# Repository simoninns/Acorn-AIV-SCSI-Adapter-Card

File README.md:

# Acorn-AIV-SCSI-Adapter-Card
A reproduction of the original Acorn AIV SCSI Adapter Card in KiCAD (as used in the BBC Domesday System)

For more information please see the [project wiki pages](https://github.com/simoninns/Acorn-AIV-SCSI-Adapter-Card/wiki)

## Synopsis

This card is designed as a drop-in replacement for the original Acorn card in the BBC Master Microcomputer and allows connection of SCSI devices (such as the Philips VP415 Domesday LaserDisc player).

The layout and routing of the board is based on the original and the board is therefore designed to use the same components.

## Motivation

The Acorn AIV SCSI board is difficult to source and commands a considerable sum on sites such as Ebay.  Using this project you are free to create your own boards for far less cost.  The design and schematics also act as a precise reference to the original design.  The original schematics are available on the web, however they are incorrect.  By recreating the board and following the original routing, the schematics included in this project are verified as correct.

## Author

The Acorn AIV SCSI Adapter Card issue 2 was designed by Simon Inns.

## License

This project is released under a Creative Commons Attribution-ShareAlike 4.0 International (CC BY-SA 4.0) licence.

You are free to:

Share — copy and redistribute the material in any medium or format
Adapt — remix, transform, and build upon the material
for any purpose, even commercially.

This license is acceptable for Free Cultural Works.

The licensor cannot revoke these freedoms as long as you follow the license terms.

Under the following terms:

Attribution — You must give appropriate credit, provide a link to the license,
and indicate if changes were made. You may do so in any reasonable manner, but
not in any way that suggests the licensor endorses you or your use.

ShareAlike — If you remix, transform, or build upon the material, you must
distribute your contributions under the same license as the original.

No additional restrictions — You may not apply legal terms or technological
measures that legally restrict others from doing anything the license permits.

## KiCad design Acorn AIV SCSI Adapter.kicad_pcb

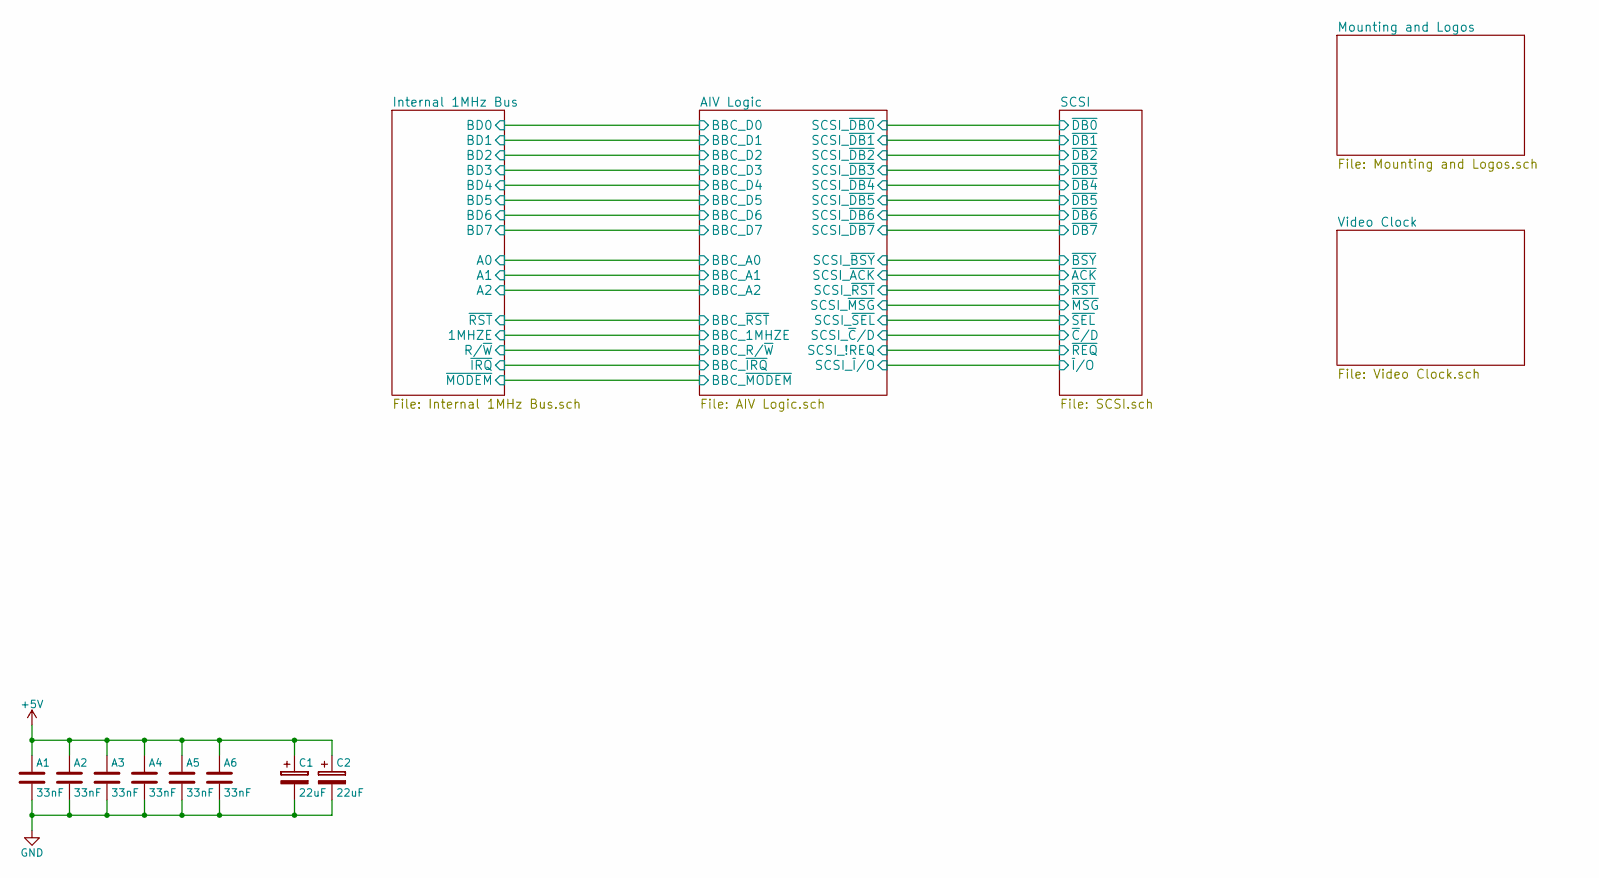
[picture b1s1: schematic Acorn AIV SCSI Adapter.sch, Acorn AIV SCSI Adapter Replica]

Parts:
A1, A2, A3, A4, A5, A6: 33nF; C_Disc_D5.0mm_W2.5mm_P5.00mm
C1, C2: 22uF; CP_Radial_Tantal_D5.0mm_P5.00mm

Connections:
+5V: A1.1, A2.1, A3.1, A4.1, A5.1, A6.1, C1.1, C2.1; also elsewhere on the board
GND: A1.2, A2.2, A3.2, A4.2, A5.2, A6.2, C1.2, C2.2; also elsewhere on the board

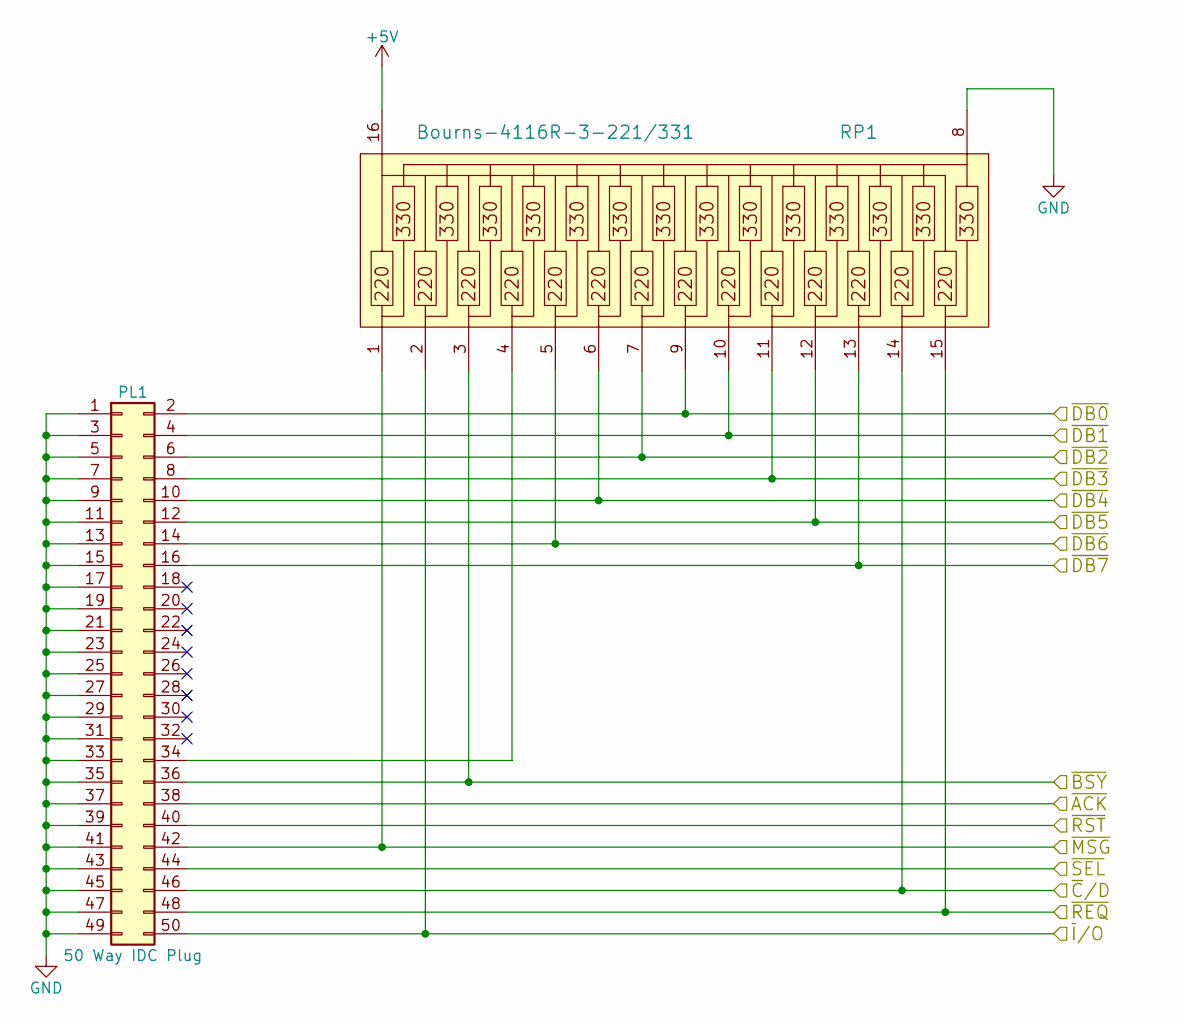
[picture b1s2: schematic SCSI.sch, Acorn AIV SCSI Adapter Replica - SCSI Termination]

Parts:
PL1: 50 Way IDC Plug; Multicomp_MC9A12-5034_2x25x2.54mm_Straight
RP1: Bourns-4116R-3-221/331; DIP-16_W7.62mm

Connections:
+5V: RP1.16; also elsewhere on the board
/AIV Logic/SCSI_!REQ: PL1.48, RP1.15; also elsewhere on the board
/AIV Logic/SCSI_~ACK: PL1.38; also elsewhere on the board
/AIV Logic/SCSI_~BSY: PL1.36, RP1.3; also elsewhere on the board
/AIV Logic/SCSI_~C~/D: PL1.46, RP1.14; also elsewhere on the board
/AIV Logic/SCSI_~DB0: PL1.2, RP1.9; also elsewhere on the board
/AIV Logic/SCSI_~DB1: PL1.4, RP1.10; also elsewhere on the board
/AIV Logic/SCSI_~DB2: PL1.6, RP1.7; also elsewhere on the board
/AIV Logic/SCSI_~DB3: PL1.8, RP1.11; also elsewhere on the board
/AIV Logic/SCSI_~DB4: PL1.10, RP1.6; also elsewhere on the board
/AIV Logic/SCSI_~DB5: PL1.12, RP1.12; also elsewhere on the board
/AIV Logic/SCSI_~DB6: PL1.14, RP1.5; also elsewhere on the board
/AIV Logic/SCSI_~DB7: PL1.16, RP1.13; also elsewhere on the board
/AIV Logic/SCSI_~I~/O: PL1.50, RP1.2; also elsewhere on the board
/AIV Logic/SCSI_~MSG: PL1.42, RP1.1; also elsewhere on the board
/AIV Logic/SCSI_~RST: PL1.40; also elsewhere on the board
/AIV Logic/SCSI_~SEL: PL1.44; also elsewhere on the board
GND: PL1.1, PL1.3, PL1.5, PL1.7, PL1.9, PL1.11, PL1.13, PL1.15, PL1.17, PL1.19, PL1.21, PL1.23, PL1.25, PL1.27, PL1.29, PL1.31, PL1.33, PL1.35, PL1.37, PL1.39, PL1.41, PL1.43, PL1.45, PL1.47, PL1.49, RP1.8; also elsewhere on the board
unnamed: PL1.34, RP1.4

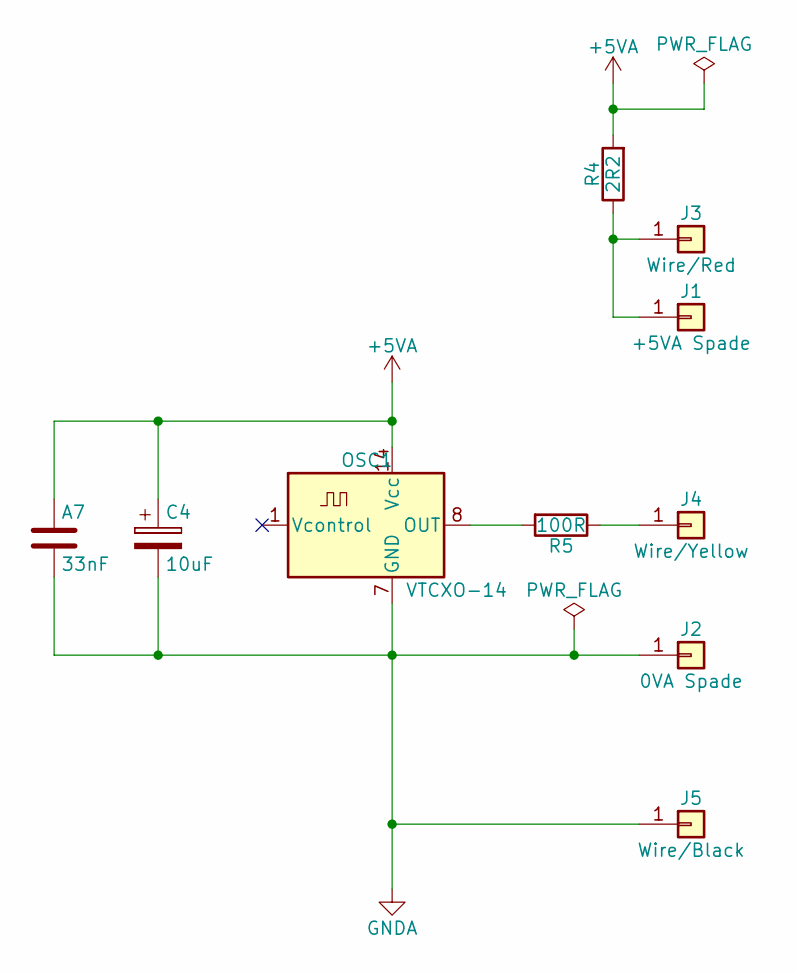
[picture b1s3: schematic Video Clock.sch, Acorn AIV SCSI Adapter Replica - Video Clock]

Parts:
A7: 33nF; C_Disc_D5.0mm_W2.5mm_P5.00mm
C4: 10uF; CP_Radial_Tantal_D5.0mm_P5.00mm
J1: +5VA Spade; PCB_Blade_Terminal_6.3mm
J2: 0VA Spade; PCB_Blade_Terminal_6.3mm
J3: Wire/Red; Pin_d1.4mm_L8.5mm_W2.8mm_FlatFork
J4: Wire/Yellow; Pin_d1.4mm_L8.5mm_W2.8mm_FlatFork
J5: Wire/Black; Pin_d1.4mm_L8.5mm_W2.8mm_FlatFork
OSC1: VTCXO-14; Oscillator_DIP-14
R4: 2R2; R_Axial_DIN0207_L6.3mm_D2.5mm_P10.16mm_Horizontal
R5: 100R; R_Axial_DIN0207_L6.3mm_D2.5mm_P10.16mm_Horizontal

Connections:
+5VA: A7.1, C4.1, OSC1.14 (Vcc), R4.2
GNDA: A7.2, C4.2, J2.1, J5.1, OSC1.7 (GND)
unnamed: J1.1, J3.1, R4.1
unnamed: J4.1, R5.1
unnamed: OSC1.8 (OUT), R5.2

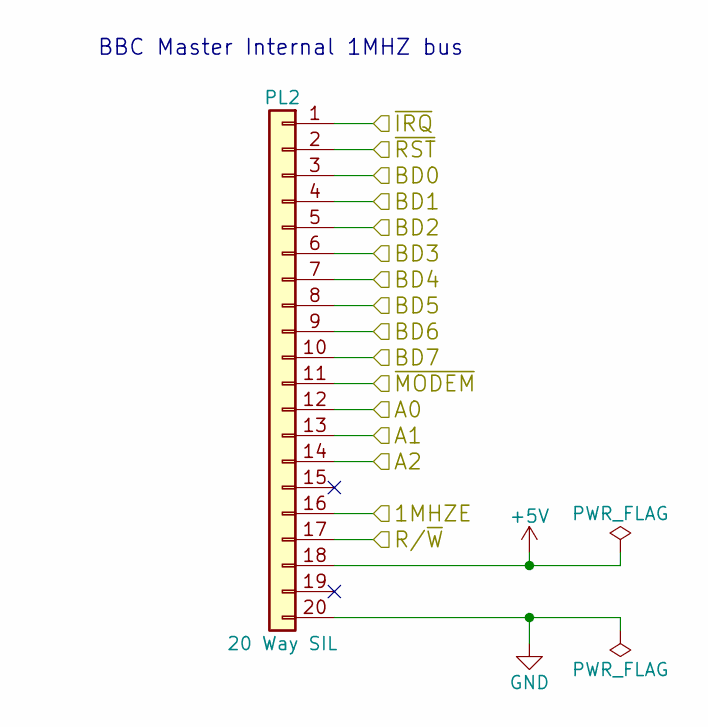
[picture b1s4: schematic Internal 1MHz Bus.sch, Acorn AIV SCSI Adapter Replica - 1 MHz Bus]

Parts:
PL2: 20 Way SIL; Pin_Header_Straight_1x20_Pitch2.54mm

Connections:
+5V: PL2.18; also elsewhere on the board
/AIV Logic/BBC_D0: PL2.3; also elsewhere on the board
/AIV Logic/BBC_D1: PL2.4; also elsewhere on the board
/AIV Logic/BBC_D2: PL2.5; also elsewhere on the board
/AIV Logic/BBC_D3: PL2.6; also elsewhere on the board
/AIV Logic/BBC_D4: PL2.7; also elsewhere on the board
/AIV Logic/BBC_D5: PL2.8; also elsewhere on the board
/AIV Logic/BBC_D6: PL2.9; also elsewhere on the board
/AIV Logic/BBC_D7: PL2.10; also elsewhere on the board
/AIV Logic/BBC_R/~W: PL2.17; also elsewhere on the board
/AIV Logic/BBC_~IRQ: PL2.1; also elsewhere on the board
/AIV Logic/BBC_~MODEM: PL2.11; also elsewhere on the board
/AIV Logic/BBC_~RST: PL2.2; also elsewhere on the board
/Internal 1MHz Bus/1MHZE: PL2.16; also elsewhere on the board
/Internal 1MHz Bus/A0: PL2.12; also elsewhere on the board
/Internal 1MHz Bus/A1: PL2.13; also elsewhere on the board
/Internal 1MHz Bus/A2: PL2.14; also elsewhere on the board
GND: PL2.20; also elsewhere on the board

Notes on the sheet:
BBC Master Internal 1MHZ bus

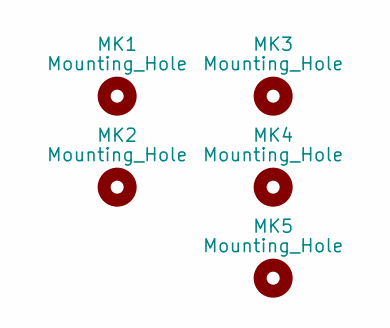
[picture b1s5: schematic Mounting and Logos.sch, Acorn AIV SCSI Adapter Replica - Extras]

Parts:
MK1, MK2, MK3, MK4, MK5: Mounting_Hole; MountingHole_3.2mm_M3

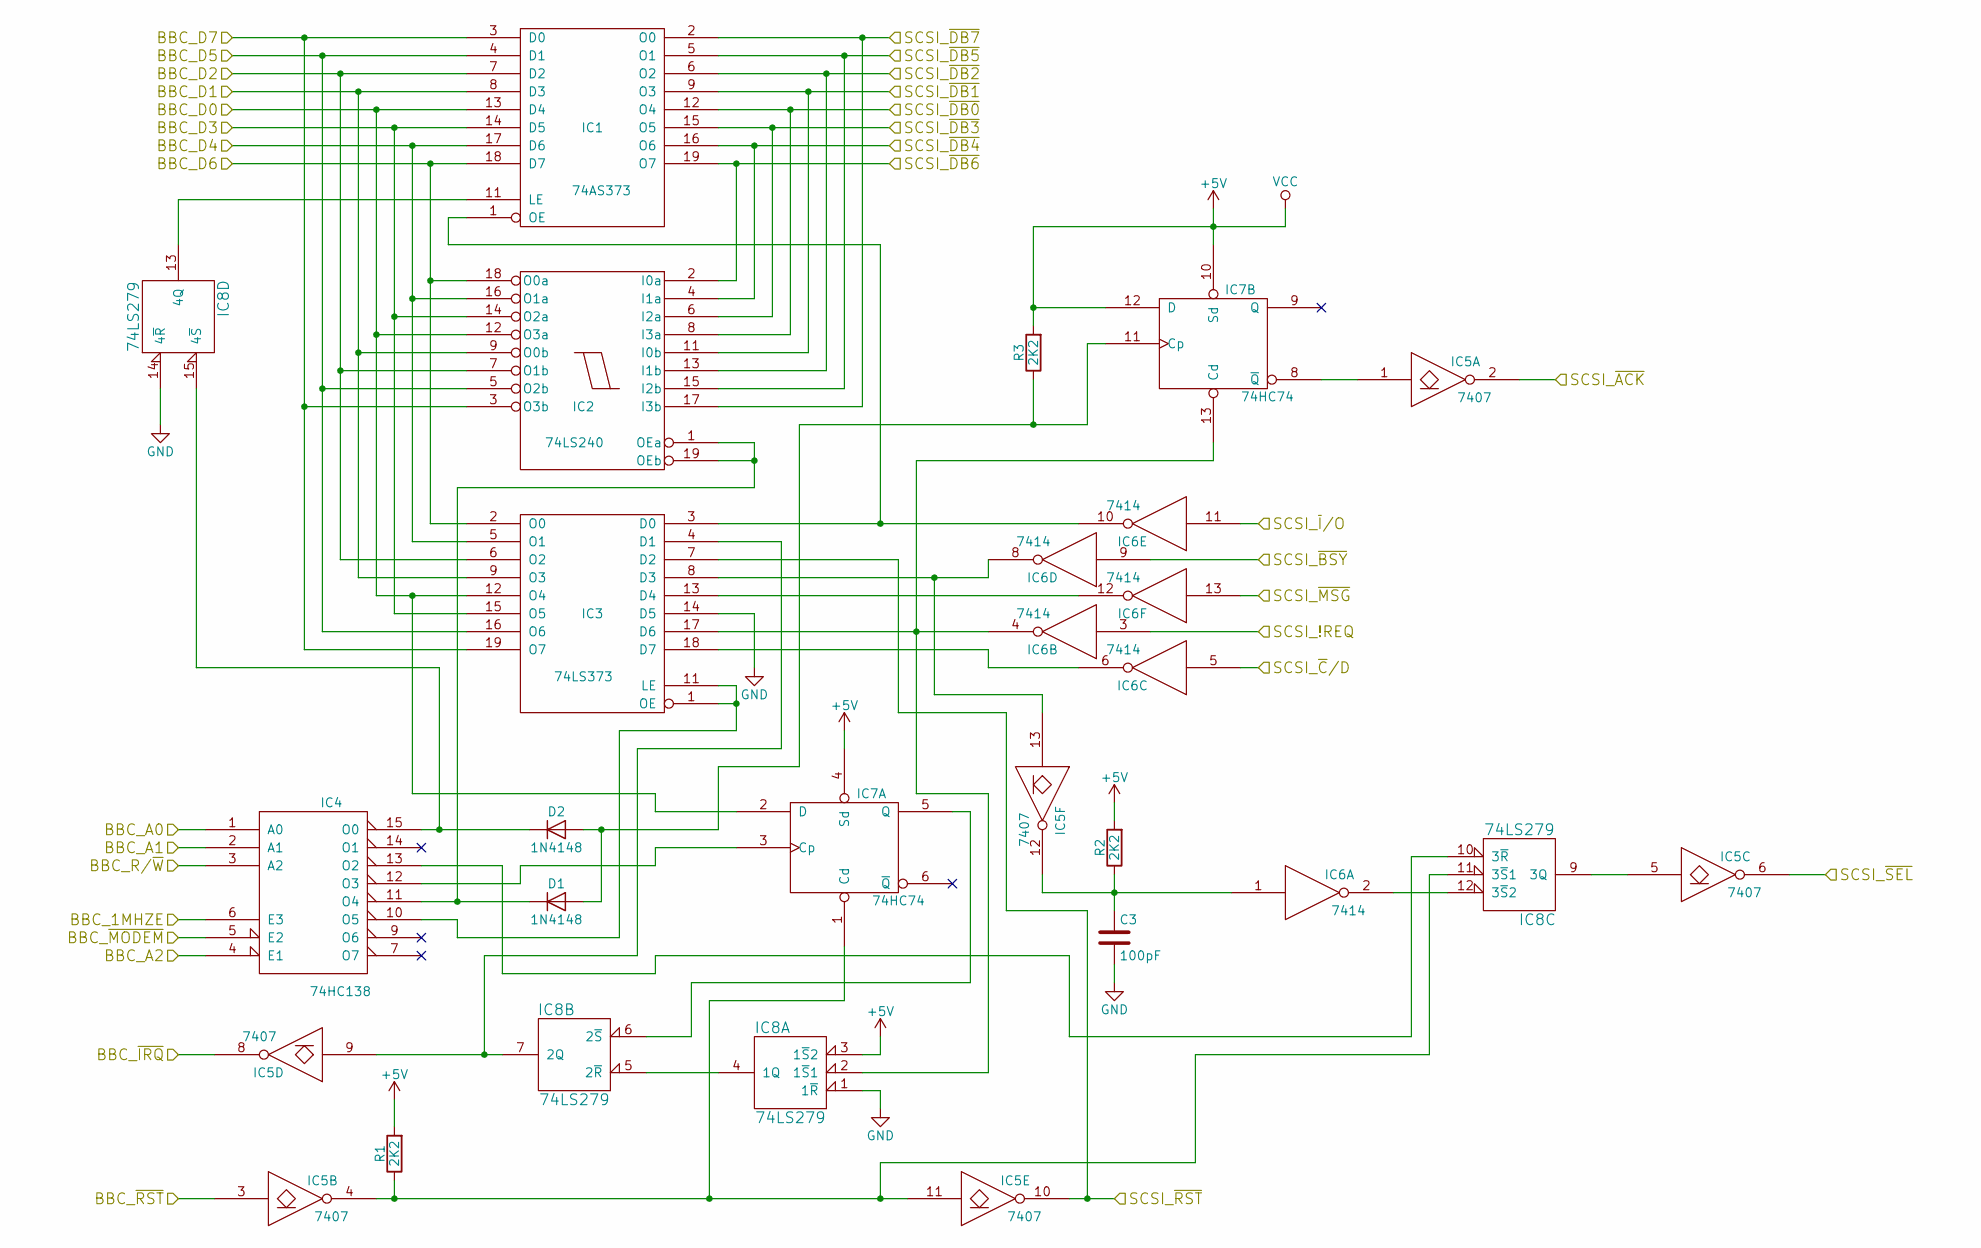
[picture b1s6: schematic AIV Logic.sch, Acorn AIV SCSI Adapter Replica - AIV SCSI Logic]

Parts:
C3: 100pF; C_Disc_D5.0mm_W2.5mm_P5.00mm
D1, D2: 1N4148; D_DO-35_SOD27_P10.16mm_Horizontal
IC1: 74AS373; DIP-20_W7.62mm
IC2: 74LS240; DIP-20_W7.62mm
IC3: 74LS373; DIP-20_W7.62mm
IC4: 74HC138; DIP-16_W7.62mm
IC5: 7407; DIP-14_W7.62mm
IC6: 7414; DIP-14_W7.62mm
IC7: 74HC74; DIP-14_W7.62mm
IC8: 74LS279; DIP-16_W7.62mm
R1, R2, R3: 2K2; R_Axial_DIN0207_L6.3mm_D2.5mm_P10.16mm_Horizontal

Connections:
+5V: IC1.20 (VCC), IC2.20 (VCC), IC3.20 (VCC), IC4.16 (VCC), IC5.14 (VCC), IC6.14 (VCC), IC7.4 (Sd), IC7.10 (Sd), IC7.12 (D), IC7.14 (VCC), IC8.3 (1~S~2), IC8.16 (Vcc), R1.2, R2.2, R3.2; also elsewhere on the board
/AIV Logic/BBC_D0: IC1.13 (D4), IC2.12 (O3a), IC3.12 (O4), IC7.2 (D); also elsewhere on the board
/AIV Logic/BBC_D1: IC1.8 (D3), IC2.9 (O0b), IC3.9 (O3); also elsewhere on the board
/AIV Logic/BBC_D2: IC1.7 (D2), IC2.7 (O1b), IC3.6 (O2); also elsewhere on the board
/AIV Logic/BBC_D3: IC1.14 (D5), IC2.14 (O2a), IC3.15 (O5); also elsewhere on the board
/AIV Logic/BBC_D4: IC1.17 (D6), IC2.16 (O1a), IC3.5 (O1); also elsewhere on the board
/AIV Logic/BBC_D5: IC1.4 (D1), IC2.5 (O2b), IC3.16 (O6); also elsewhere on the board
/AIV Logic/BBC_D6: IC1.18 (D7), IC2.18 (O0a), IC3.2 (O0); also elsewhere on the board
/AIV Logic/BBC_D7: IC1.3 (D0), IC2.3 (O3b), IC3.19 (O7); also elsewhere on the board
/AIV Logic/BBC_R/~W: IC4.3 (A2); also elsewhere on the board
/AIV Logic/BBC_~IRQ: IC5.8; also elsewhere on the board
/AIV Logic/BBC_~MODEM: IC4.5 (E2); also elsewhere on the board
/AIV Logic/BBC_~RST: IC5.3; also elsewhere on the board
/AIV Logic/SCSI_!REQ: IC6.3; also elsewhere on the board
/AIV Logic/SCSI_~ACK: IC5.2; also elsewhere on the board
/AIV Logic/SCSI_~BSY: IC6.9; also elsewhere on the board
/AIV Logic/SCSI_~C~/D: IC6.5; also elsewhere on the board
/AIV Logic/SCSI_~DB0: IC1.12 (O4), IC2.8 (I3a); also elsewhere on the board
/AIV Logic/SCSI_~DB1: IC1.9 (O3), IC2.11 (I0b); also elsewhere on the board
/AIV Logic/SCSI_~DB2: IC1.6 (O2), IC2.13 (I1b); also elsewhere on the board
/AIV Logic/SCSI_~DB3: IC1.15 (O5), IC2.6 (I2a); also elsewhere on the board
/AIV Logic/SCSI_~DB4: IC1.16 (O6), IC2.4 (I1a); also elsewhere on the board
/AIV Logic/SCSI_~DB5: IC1.5 (O1), IC2.15 (I2b); also elsewhere on the board
/AIV Logic/SCSI_~DB6: IC1.19 (O7), IC2.2 (I0a); also elsewhere on the board
/AIV Logic/SCSI_~DB7: IC1.2 (O0), IC2.17 (I3b); also elsewhere on the board
/AIV Logic/SCSI_~I~/O: IC6.11; also elsewhere on the board
/AIV Logic/SCSI_~MSG: IC6.13; also elsewhere on the board
/AIV Logic/SCSI_~RST: IC3.7 (D2), IC5.10; also elsewhere on the board
/AIV Logic/SCSI_~SEL: IC5.6; also elsewhere on the board
/Internal 1MHz Bus/1MHZE: IC4.6 (E3); also elsewhere on the board
/Internal 1MHz Bus/A0: IC4.1 (A0); also elsewhere on the board
/Internal 1MHz Bus/A1: IC4.2 (A1); also elsewhere on the board
/Internal 1MHz Bus/A2: IC4.4 (E1); also elsewhere on the board
GND: C3.2, IC1.10 (GND), IC2.10 (GND), IC3.10 (GND), IC3.14 (D5), IC4.8 (GND), IC5.7 (GND), IC6.7 (GND), IC7.7 (GND), IC8.1 (1~R), IC8.8 (GND), IC8.14 (4~R); also elsewhere on the board
unnamed: C3.1, IC5.12, IC6.1, R2.1
unnamed: D1.1 (K), IC2.1 (OEa), IC2.19 (OEb), IC4.11 (O4)
unnamed: D1.2 (A), D2.2 (A), IC7.11 (Cp), R3.1
unnamed: D2.1 (K), IC4.15 (O0), IC8.15 (4~S)
unnamed: IC1.1 (OE), IC3.3 (D0), IC6.10
unnamed: IC1.11 (LE), IC8.13 (4Q)
unnamed: IC3.1 (OE), IC3.11 (LE), IC4.10 (O5)
unnamed: IC3.4 (D1), IC5.9, IC8.7 (2Q)
unnamed: IC3.8 (D3), IC5.13, IC6.8
unnamed: IC3.13 (D4), IC6.12
unnamed: IC3.17 (D6), IC6.4, IC7.13 (Cd), IC8.2 (1~S~1)
unnamed: IC3.18 (D7), IC6.6
unnamed: IC4.12 (O3), IC7.3 (Cp)
unnamed: IC4.13 (O2), IC8.10 (3~R)
unnamed: IC5.1, IC7.8 (~Q)
unnamed: IC5.5, IC8.9 (3Q)
unnamed: IC5.4, IC5.11, IC7.1 (Cd), IC8.11 (3~S~1), R1.1
unnamed: IC6.2, IC8.12 (3~S~2)
unnamed: IC7.5 (Q), IC8.6 (2~S)
unnamed: IC8.4 (1Q), IC8.5 (2~R)

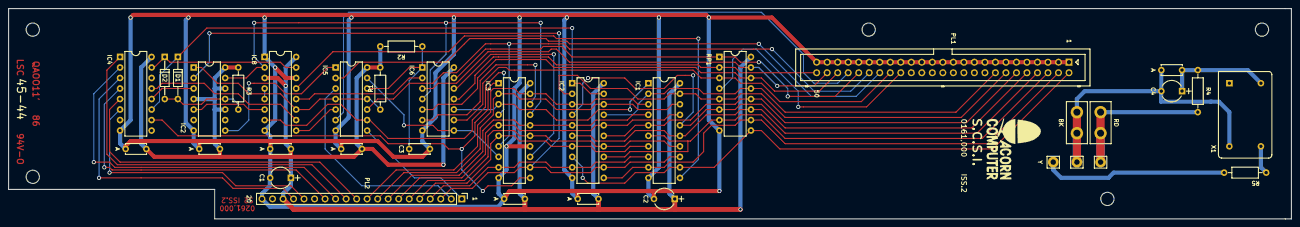
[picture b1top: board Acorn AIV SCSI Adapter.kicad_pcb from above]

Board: 2 copper layers, 309.9 x 50.8 mm, 40 parts (0 on the bottom side), 60 nets.

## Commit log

2018-04-29 Initial release of project to Github
2018-05-01 Added CC License text
2018-05-04 Added back-copper ground plane fill and updated gerbers
2018-05-27 FIxed issue #1
2018-07-01 Corrected mounting holes and silkscreen
2018-08-11 Adjustment to mounting holes for better alignment
2022-12-19 Added wiki link to readme

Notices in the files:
AIV Logic.sch:
(c)2018 Simon Inns
License: Attribution-ShareAlike 4.0 International (CC BY-SA 4.0)
